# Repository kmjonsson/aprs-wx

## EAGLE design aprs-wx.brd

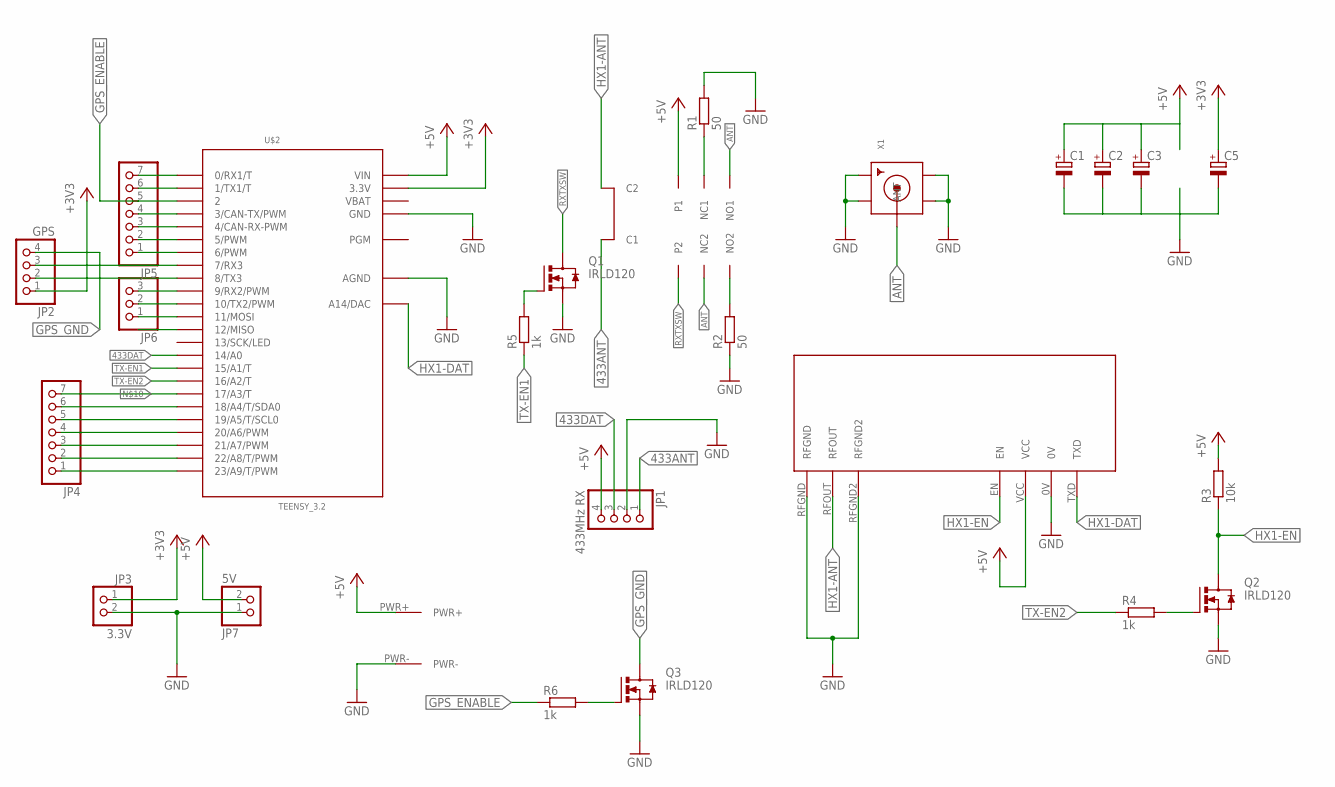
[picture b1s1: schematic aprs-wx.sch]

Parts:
BTPL1: GS-SH-2XXT5V; GOODSKY_RELAY
C1, C2, C3, C5: CPOL-EUE2,5-6E; E2,5-6E
JP1: 433MHz RX; 1X04
JP2: GPS; 1X04
JP3: 3.3V; 1X02
JP4, JP5: PINHD-1X7; 1X07
JP6: PINHD-1X3; 1X03
JP7: 5V; 1X02
Q1, Q2, Q3: IRLD120; HVMDIP
R1, R2: 50; 0207/10
R3: 10k; 0207/10
R4, R5, R6: 1k; 0207/10
U$1: RADIOMETRIX-HX1
U$2: TEENSY_3.2; TEENSY_3.0-3.2&LC_OUTER_ROW
U$3: SOLDERPWR-1
X1: SMACONNECTOR_EDGE; SMA_EDGELAUNCH

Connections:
433ANT: BTPL1.P2 (C1), JP1.1
433DAT: JP1.3, U$2.14/A0
+3V3: C5.+, JP2.1, JP3.1, U$2.3.3V, U$2.3.3V1 (3.3V)
+5V: BTPL1.C2 (P1), C1.+, C2.+, C3.+, JP1.4, JP7.2, R3.2, U$1.VCC, U$2.VIN, U$3.PWR+
ANT: BTPL1.NC2 (NO1), BTPL1.NO1 (NC2), X1.P (ANT)
GND: C1.-, C2.-, C3.-, C5.-, JP1.2, JP3.2, JP7.1, Q1.S, Q2.S, Q3.S, R1.2, R2.1, U$1.0V, U$1.RFGND, U$1.RFGND2, U$2.AGND, U$2.GND, U$2.GND1 (GND), U$3.PWR-, X1.GND@1 (GND4), X1.GND@2 (GND3), X1.GND@3 (GND2), X1.GND@4 (GND1)
GPS_ENABLE: JP5.5, R6.1, U$2.2
GPS_GND: JP2.4, Q3.D@1 (D), Q3.D@2 (D)
HX1-ANT: BTPL1.P1 (C2), U$1.RFOUT
HX1-DAT: U$1.TXD, U$2.RESET/DAC (A14/DAC)
HX1-EN: Q2.D@1 (D), Q2.D@2 (D), R3.1, U$1.EN
unnamed: BTPL1.NO2 (NC1), R1.1
unnamed: Q2.G, R4.2
unnamed: Q1.G, R5.2
unnamed: BTPL1.NC1 (NO2), R2.2
unnamed: JP2.2, U$2.8 (8/TX3)
unnamed: JP2.3, U$2.7 (7/RX3)
unnamed: JP4.1, U$2.23/A9 (23/A9/T/PWM)
unnamed: JP4.2, U$2.22/A8 (22/A8/T/PWM)
unnamed: JP4.7, U$2.17/A3 (17/A3/T)
unnamed: JP4.3, U$2.21/A7 (21/A7/PWM)
unnamed: JP4.4, U$2.20/A6 (20/A6/PWM)
unnamed: JP4.5, U$2.19/A5 (19/A5/T/SCL0)
unnamed: JP4.6, U$2.18/A4 (18/A4/T/SDA0)
unnamed: JP5.7, U$2.0 (0/RX1/T)
unnamed: JP5.6, U$2.1 (1/TX1/T)
unnamed: JP5.4, U$2.3 (3/CAN-TX/PWM)
unnamed: JP5.3, U$2.4 (4/CAN-RX-PWM)
unnamed: JP5.2, U$2.5 (5/PWM)
unnamed: JP5.1, U$2.6 (6/PWM)
unnamed: JP6.3, U$2.9 (9/RX2/PWM)
unnamed: JP6.2, U$2.10 (10/TX2/PWM)
unnamed: JP6.1, U$2.11 (11/MOSI)
unnamed: Q3.G, R6.2
RXTXSW: BTPL1.C1 (P2), Q1.D@1 (D), Q1.D@2 (D)
TX-EN1: R5.1, U$2.15/A1 (15/A1/T)
TX-EN2: R4.1, U$2.16/A2 (16/A2/T)
VBAT: U$2.VBAT

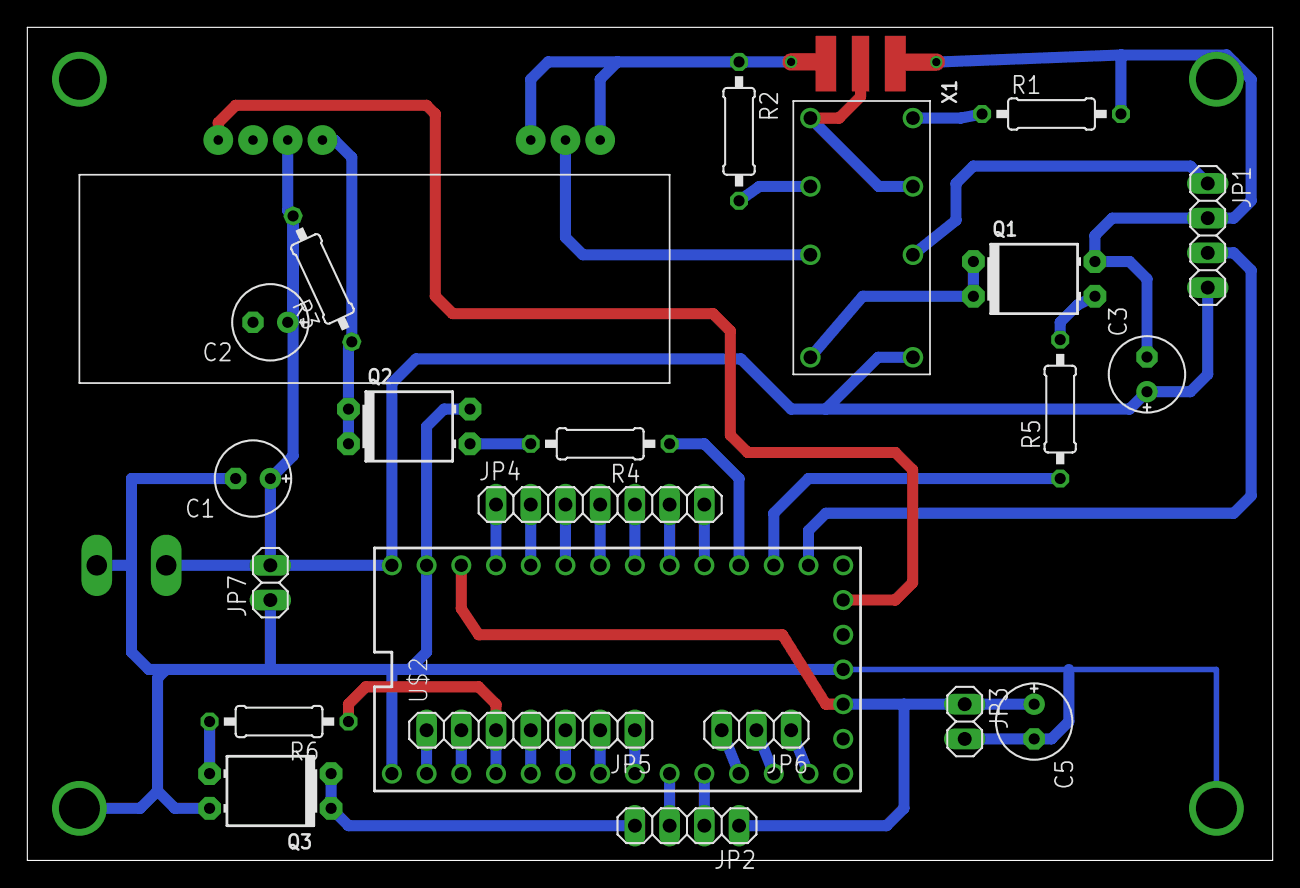
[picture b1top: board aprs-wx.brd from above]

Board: 2 copper layers, 91.1 x 61.0 mm, 25 parts (0 on the bottom side), 37 nets.

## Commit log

2018-05-08 First commit. (v1.0)
